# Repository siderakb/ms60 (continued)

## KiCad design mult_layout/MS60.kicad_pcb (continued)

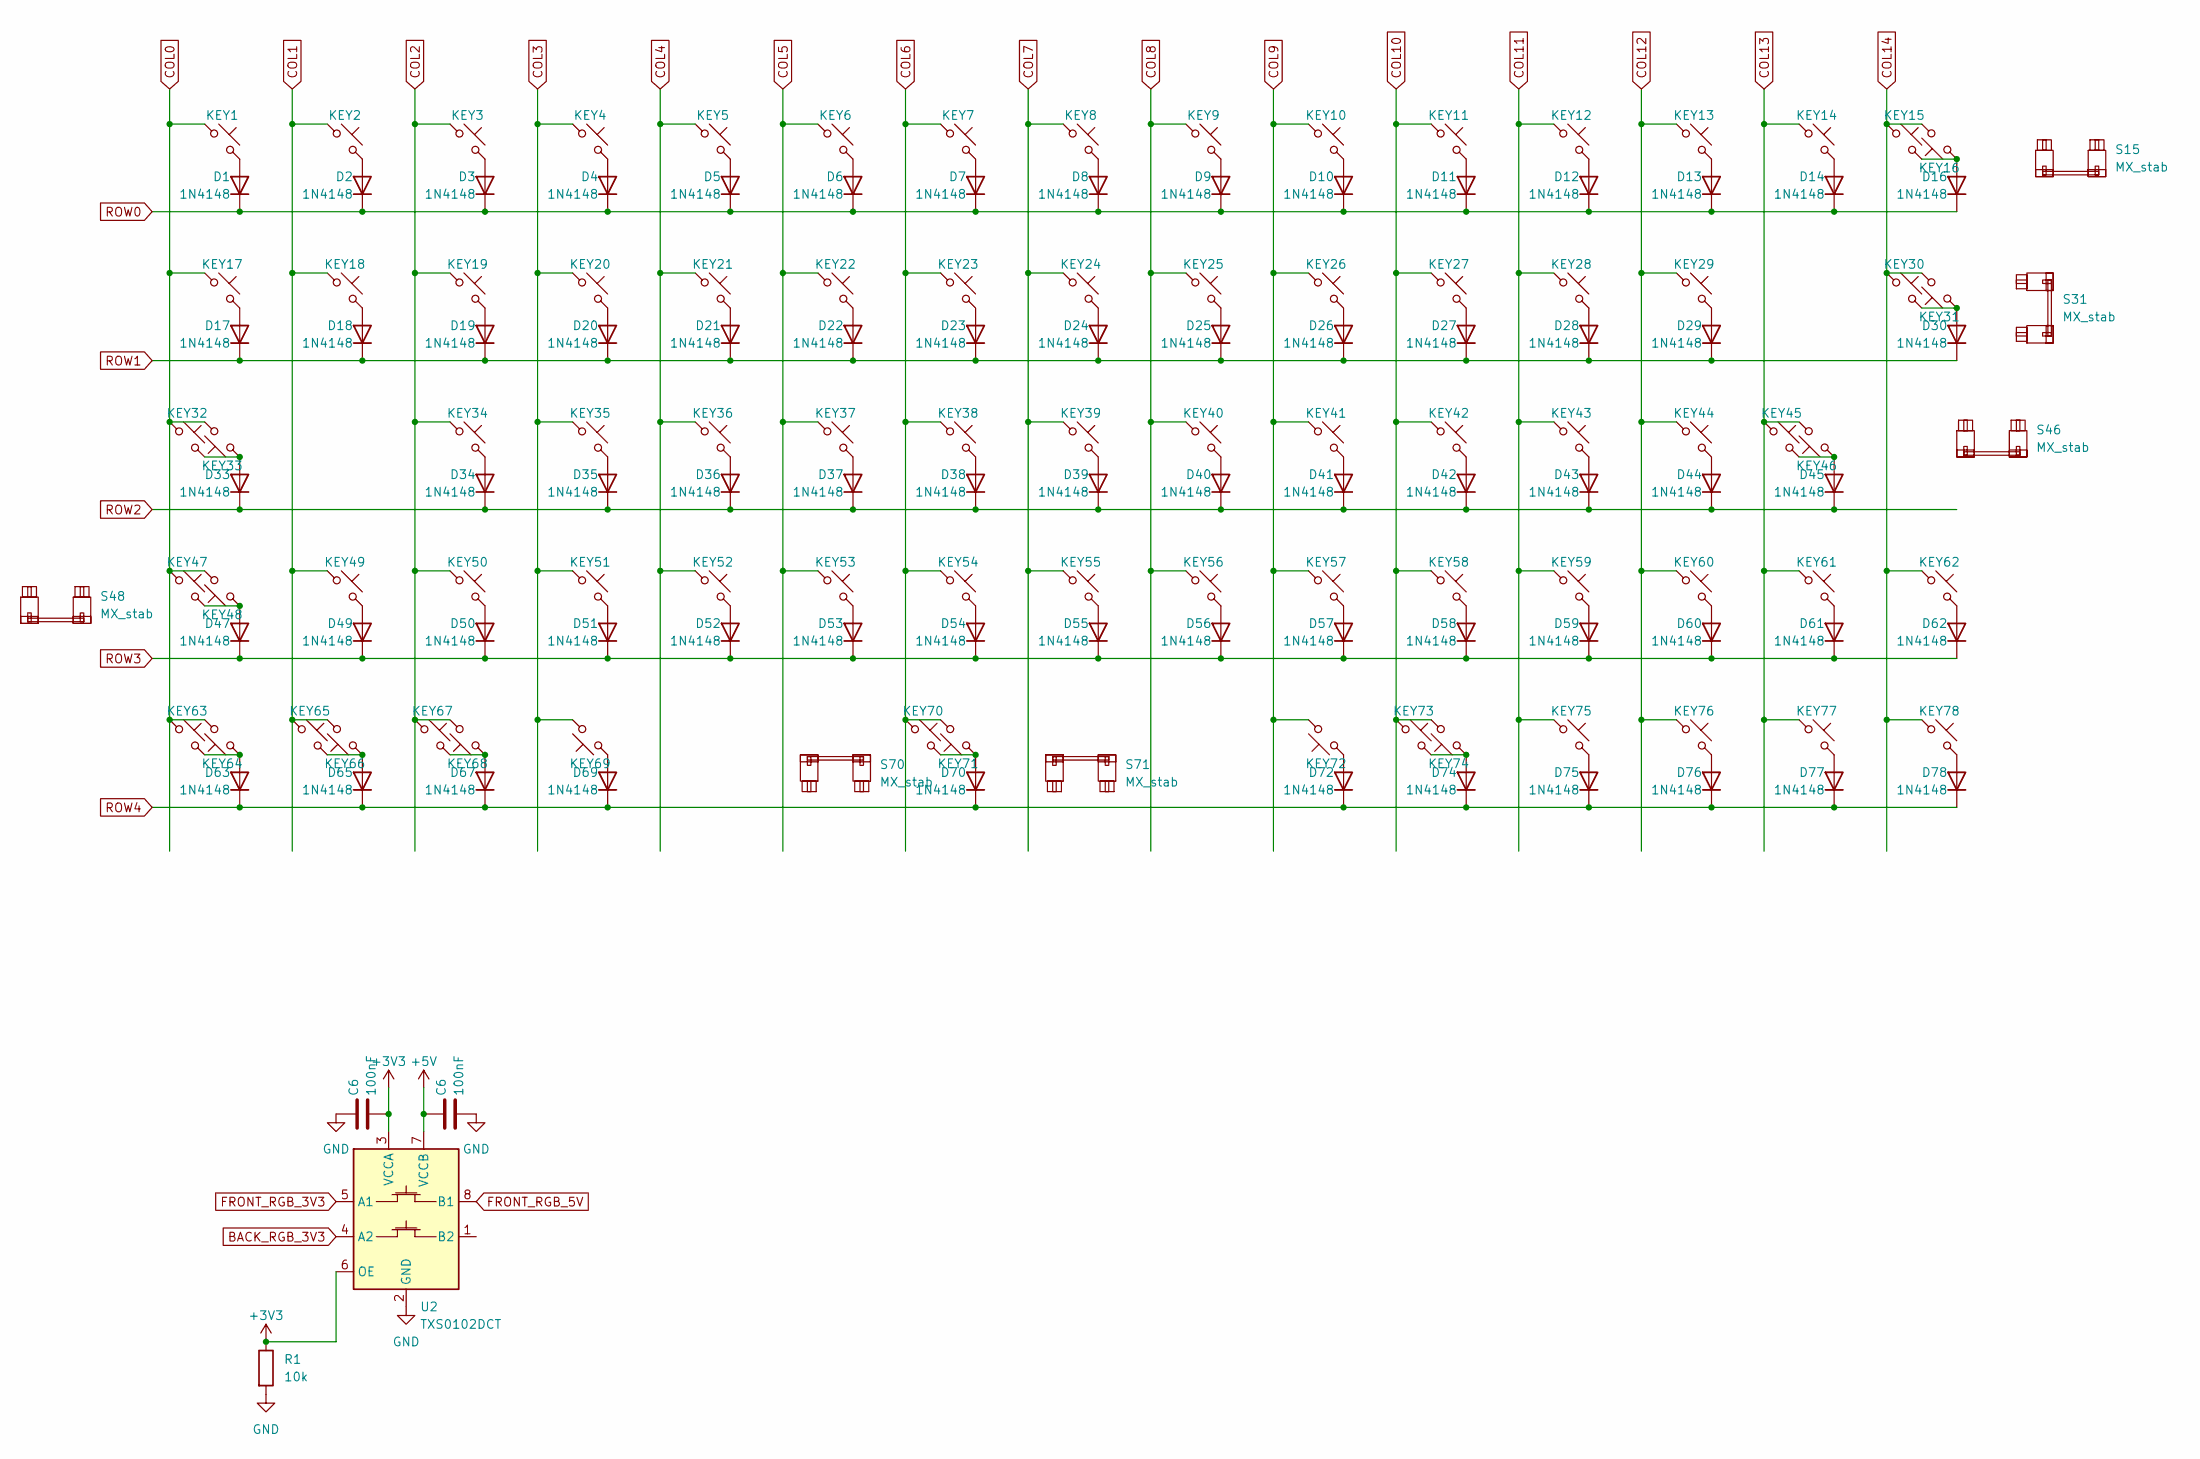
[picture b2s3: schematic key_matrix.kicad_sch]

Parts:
C6: 100nF; C_0402_1005Metric; MFR. Part # CL05B104KO5NNNC; LCSC C1525
D1, D2, D3, D4, D5, D6, D7, D8, D9, D10, D11, D12, D13, D14, D16, D17, D18, D19, D20, D21, D22, D23, D24, D25, D26, D27, D28, D29, D30, D33, D34, D35, D36, D37, D38, D39, D40, D41, D42, D43, D44, D45, D47, D49, D50, D51, D52, D53, D54, D55, D56, D57, D58, D59, D60, D61, D62, D63, D65, D67, D69, D70, D72, D74, D75, D76, D77, D78: 1N4148; D_SOD-323_HandSoldering; MFR. Part # 1N4148W; LCSC C81598
KEY1, KEY2, KEY3, KEY4, KEY5, KEY6, KEY7, KEY8, KEY9, KEY10, KEY11, KEY12, KEY13, KEY14, KEY15, KEY16, KEY17, KEY18, KEY19, KEY20, KEY21, KEY22, KEY23, KEY24, KEY25, KEY26, KEY27, KEY28, KEY29, KEY30, KEY31, KEY32, KEY33, KEY34, KEY35, KEY36, KEY37, KEY38, KEY39, KEY40, KEY41, KEY42, KEY43, KEY44, KEY45, KEY46, KEY47, KEY48, KEY49, KEY50, KEY51, KEY52, KEY53, KEY54, KEY55, KEY56, KEY57, KEY58, KEY59, KEY60, KEY61, KEY62, KEY63, KEY64, KEY65, KEY66, KEY67, KEY68, KEY69, KEY70, KEY71, KEY72, KEY73, KEY74, KEY75, KEY76, KEY77, KEY78: SW_Push_45deg; SW_MX_HotSwap
R1: 10k
S15, S48: MX_stab; STAB_MX_2u
S31: MX_stab; STAB_MX_ISO
S46: MX_stab; STAB_MX_2.25u
S70: MX_stab; STAB_MX_6.25u
S71: MX_stab; STAB_MX_3u
U2: TXS0102DCT; SSOP-8_2.95x2.8mm_P0.65mm

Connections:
BACK_RGB_3V3: U2.4 (A2)
COL0: KEY1.1, KEY17.1, KEY32.1, KEY33.2, KEY47.1, KEY48.2, KEY63.1, KEY64.2
COL1: KEY2.1, KEY18.1, KEY49.1, KEY65.1, KEY66.2
COL2: KEY3.1, KEY19.1, KEY34.1, KEY50.1, KEY67.1, KEY68.2
COL3: KEY4.1, KEY20.1, KEY35.1, KEY51.1, KEY69.2
COL4: KEY5.1, KEY21.1, KEY36.1, KEY52.1
COL5: KEY6.1, KEY22.1, KEY37.1, KEY53.1
COL6: KEY7.1, KEY23.1, KEY38.1, KEY54.1, KEY70.1, KEY71.2
COL7: KEY8.1, KEY24.1, KEY39.1, KEY55.1
COL8: KEY9.1, KEY25.1, KEY40.1, KEY56.1
COL9: KEY10.1, KEY26.1, KEY41.1, KEY57.1, KEY72.2
COL10: KEY11.1, KEY27.1, KEY42.1, KEY58.1, KEY73.1, KEY74.2
COL11: KEY12.1, KEY28.1, KEY43.1, KEY59.1, KEY75.1
COL12: KEY13.1, KEY29.1, KEY44.1, KEY60.1, KEY76.1
COL13: KEY14.1, KEY45.1, KEY46.2, KEY61.1, KEY77.1
COL14: KEY15.1, KEY16.2, KEY30.1, KEY31.2, KEY62.1, KEY78.1
FRONT_RGB_3V3: U2.5 (A1)
FRONT_RGB_5V: U2.8 (B1)
unnamed: D1.2 (A), KEY1.2
unnamed: D2.2 (A), KEY2.2
unnamed: D3.2 (A), KEY3.2
unnamed: D4.2 (A), KEY4.2
unnamed: D5.2 (A), KEY5.2
unnamed: D6.2 (A), KEY6.2
unnamed: D7.2 (A), KEY7.2
unnamed: D8.2 (A), KEY8.2
unnamed: D9.2 (A), KEY9.2
unnamed: D10.2 (A), KEY10.2
unnamed: D11.2 (A), KEY11.2
unnamed: D12.2 (A), KEY12.2
unnamed: D13.2 (A), KEY13.2
unnamed: D14.2 (A), KEY14.2
unnamed: D16.2 (A), KEY15.2, KEY16.1
unnamed: D17.2 (A), KEY17.2
unnamed: D18.2 (A), KEY18.2
unnamed: D19.2 (A), KEY19.2
unnamed: D20.2 (A), KEY20.2
unnamed: D21.2 (A), KEY21.2
unnamed: D22.2 (A), KEY22.2
unnamed: D23.2 (A), KEY23.2
unnamed: D24.2 (A), KEY24.2
unnamed: D25.2 (A), KEY25.2
unnamed: D26.2 (A), KEY26.2
unnamed: D27.2 (A), KEY27.2
unnamed: D28.2 (A), KEY28.2
unnamed: D29.2 (A), KEY29.2
unnamed: D30.2 (A), KEY30.2, KEY31.1
unnamed: D33.2 (A), KEY32.2, KEY33.1
unnamed: D34.2 (A), KEY34.2
unnamed: D35.2 (A), KEY35.2
unnamed: D36.2 (A), KEY36.2
unnamed: D37.2 (A), KEY37.2
unnamed: D38.2 (A), KEY38.2
unnamed: D39.2 (A), KEY39.2
unnamed: D40.2 (A), KEY40.2
unnamed: D41.2 (A), KEY41.2
unnamed: D42.2 (A), KEY42.2
unnamed: D43.2 (A), KEY43.2
unnamed: D44.2 (A), KEY44.2
unnamed: D45.2 (A), KEY45.2, KEY46.1
unnamed: D47.2 (A), KEY47.2, KEY48.1
unnamed: D49.2 (A), KEY49.2
unnamed: D50.2 (A), KEY50.2
unnamed: D51.2 (A), KEY51.2
unnamed: D52.2 (A), KEY52.2
unnamed: D53.2 (A), KEY53.2
unnamed: D54.2 (A), KEY54.2
unnamed: D55.2 (A), KEY55.2
unnamed: D56.2 (A), KEY56.2
unnamed: D57.2 (A), KEY57.2
unnamed: D58.2 (A), KEY58.2
unnamed: D59.2 (A), KEY59.2
unnamed: D60.2 (A), KEY60.2
unnamed: D61.2 (A), KEY61.2
unnamed: D62.2 (A), KEY62.2
unnamed: D63.2 (A), KEY63.2, KEY64.1
unnamed: D65.2 (A), KEY65.2, KEY66.1
unnamed: D67.2 (A), KEY67.2, KEY68.1
unnamed: D69.2 (A), KEY69.1
unnamed: D70.2 (A), KEY70.2, KEY71.1
unnamed: D72.2 (A), KEY72.1
unnamed: D74.2 (A), KEY73.2, KEY74.1
unnamed: D75.2 (A), KEY75.2
unnamed: D76.2 (A), KEY76.2
unnamed: D77.2 (A), KEY77.2
unnamed: D78.2 (A), KEY78.2
ROW0: D1.1 (K), D2.1 (K), D3.1 (K), D4.1 (K), D5.1 (K), D6.1 (K), D7.1 (K), D8.1 (K), D9.1 (K), D10.1 (K), D11.1 (K), D12.1 (K), D13.1 (K), D14.1 (K), D16.1 (K)
ROW1: D17.1 (K), D18.1 (K), D19.1 (K), D20.1 (K), D21.1 (K), D22.1 (K), D23.1 (K), D24.1 (K), D25.1 (K), D26.1 (K), D27.1 (K), D28.1 (K), D29.1 (K), D30.1 (K)
ROW2: D33.1 (K), D34.1 (K), D35.1 (K), D36.1 (K), D37.1 (K), D38.1 (K), D39.1 (K), D40.1 (K), D41.1 (K), D42.1 (K), D43.1 (K), D44.1 (K), D45.1 (K)
ROW3: D47.1 (K), D49.1 (K), D50.1 (K), D51.1 (K), D52.1 (K), D53.1 (K), D54.1 (K), D55.1 (K), D56.1 (K), D57.1 (K), D58.1 (K), D59.1 (K), D60.1 (K), D61.1 (K), D62.1 (K)
ROW4: D63.1 (K), D65.1 (K), D67.1 (K), D69.1 (K), D70.1 (K), D72.1 (K), D74.1 (K), D75.1 (K), D76.1 (K), D77.1 (K), D78.1 (K)

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
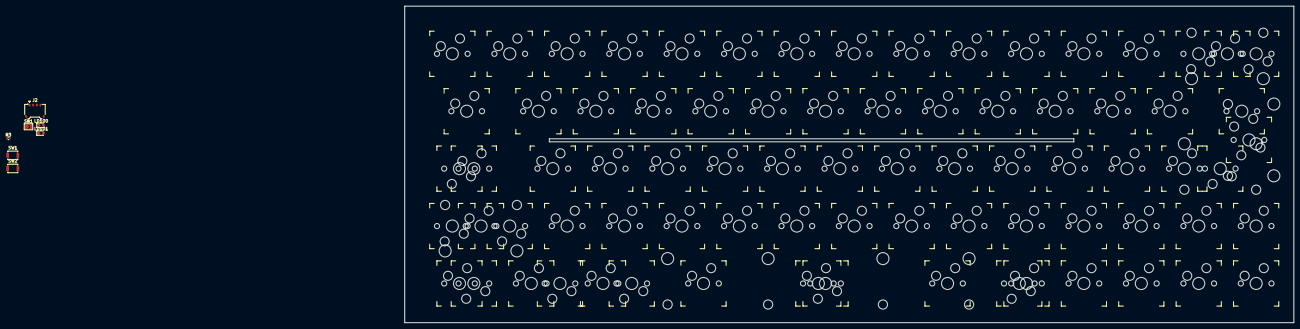
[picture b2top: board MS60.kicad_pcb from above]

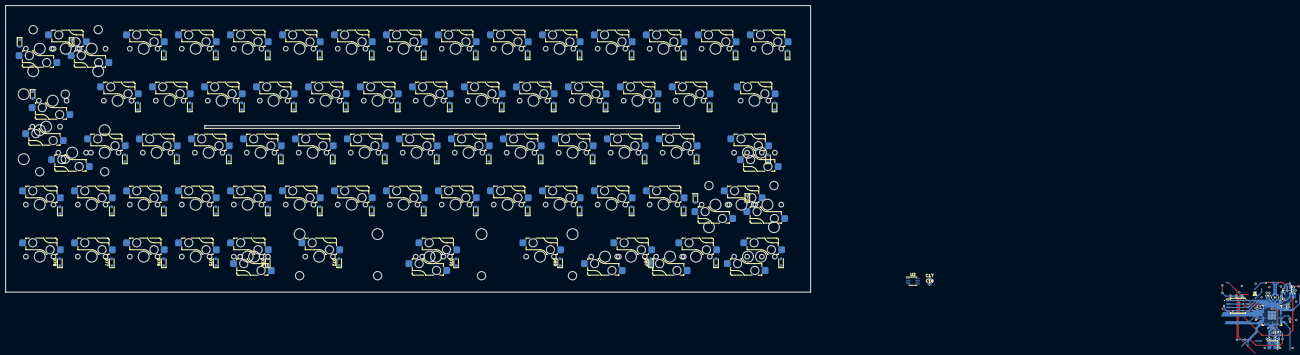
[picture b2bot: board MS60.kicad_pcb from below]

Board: 2 copper layers, 295.0 x 105.0 mm, 188 parts (97 on the bottom side), 110 nets.

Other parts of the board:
C17, C18: 100nF; C_0402_1005Metric

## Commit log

2023-09-02 Init commit
2023-09-02 Add footprint submodule
2023-09-02 Create LICENSE
2023-10-29 Update submodule (footprint library)
2023-10-29 Rename folder
2023-11-12 Add 2U left Shift edition
2023-11-12 Add license and readme
